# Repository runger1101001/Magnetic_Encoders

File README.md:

# Small encoder boards

Several designs for small magnetic encoder boards.
These boards all serve the same purpose, and many have the same shapes. They use different sensor ICs, which depending on the IC may result in different performance or different interface types.

They are intended to sense the absolute angular position of a rotating magnet. Generally this is used to sense the position of a motor shaft, as an input to motor control algorithms, or a joint/actuator position, for robotics applcations.

Where sensors use I2C, they use the Stemma-QT/Qwiic connectors (JST-SH) and pinouts.
Where sensors use SPI or SSI, they all use the same pinouts.

:warning: Not all of these have been produced or tested.

Please consult the individual subdirectories for more information. If a sub-directory does not contain a README, use at your own risk.

## Finished and tested designs

- [AS5048A](./Encoder_SPI/)
- [AS5048B](./Encoder/)
- [TLE5012B](./Encoder_SPI_TLE5012B/)
- [SC60228](./Encoder_SPI_SC60228/)

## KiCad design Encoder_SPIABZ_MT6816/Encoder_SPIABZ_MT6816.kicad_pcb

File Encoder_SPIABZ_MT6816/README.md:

# MT6816 magnetic angle sensor

Small (21x17mm) board for the MT6816 magnetic absolute angle sensor.

For use in motor control or robotics applications, the sensor measures the orientation (angle in the plane) of a nearby diametrically magnetized magnet.

That sounds more complicated than using it really is, so lets describe it another way:

- attach the magnet to the axis of something that rotates
- put the sensor near it
- read angles with your Arduino

| Back of board                                                               | Front of board                                                    |
| --------------------------------------------------------------------------- | ----------------------------------------------------------------- |
| with SH 1.0 connectors <br> | with sensor <br> |

## Features

- 3V to 5.5V operation
- 14 bit accuracy, 16384 positions per revolution
- SPI interface up to 15MHz
- PWM output pin with 1kHz PWM frequency and 12bit accuracy
- ABZ interface with 12 bit accuracy, 4096 steps in quadrature mode
- power indication LED (green, dim)

Datasheet of the sensor: https://www.novosns.com/enfiles/MT6816_Rev.2.1.pdf

## Getting one

You may be able to buy some here:

Or you could make one - it is open source, you will find gerber files and BOM in the repo, and design files for KiCad 6.

## Usage

The sensor has to be precisely positioned near the magnet. The magnet should be precisely on-axis and in-plane (no wobble!). The sensor should be mounted with an air-gap of about 0.5mm to the magnet.

Taking the time to mount the magnet and sensor board carefully will improve the accuracy and smoothness of your readings.

The sensor has SPI and ABZ interfaces, selectable by switch:

| SPI                                           | ABZ                                           |
| --------------------------------------------- | --------------------------------------------- |
|  |  |

The SPI and ABZ interfaces are output on a JST-SH 6-pin socket. Pre-made cables are available cheaply on AliExpress and other sources.

You may connect VCC to either 3.3V or 5V.

For SPI, connect the other lines (MOSI, MISO, CLK and CS) to the respective counterparts on your MCU board.
Note: The sensor board does not pull the CS line up.

The ABZ and SPI outputs cannot be used at the same time. Use the switch to select the output mode.

## Communications

SPI interface:

- SPI Mode 3
- MSB first
- max 15MHz SPI clock

See [datasheet](https://www.novosns.com/enfiles/MT6816_Rev.2.1.pdf) for details, or use an existing software driver.

:warning: Note: cable length, shielding (or lack thereof) and environmental noise may limit performance to significantly less than the 10MHz maximum.

## Software

The sensor can be used with any appropriate SPI driver.

The author uses it with Arduino-compatible MCU boards and the [SimpleFOC library](http://www.simplefoc.com).

A driver for the sensor for Arduino and SimpleFOC can be found here: [SimpleFOC drivers library](https://github.com/simplefoc/Arduino-FOC-drivers/tree/master/src/encoders/mt6816)

## Physical dimensions

v1.0: 21 x 17 x 4mm (1.6mm PCB)

## Cables

Pre-made JST SH 1.0 cables are available. When buying cables with two plugs, choose the type that is called "reverse connection" - where the pins on both ends of the cable have the same order.

Some links to compatible cables / breakout boards:

- https://www.tindie.com/products/26431/
- https://www.aliexpress.com/item/4000421829259.html
- https://www.aliexpress.com/item/4001235017139.html
- https://www.pololu.com/product/4770
- https://www.pololu.com/product/4772

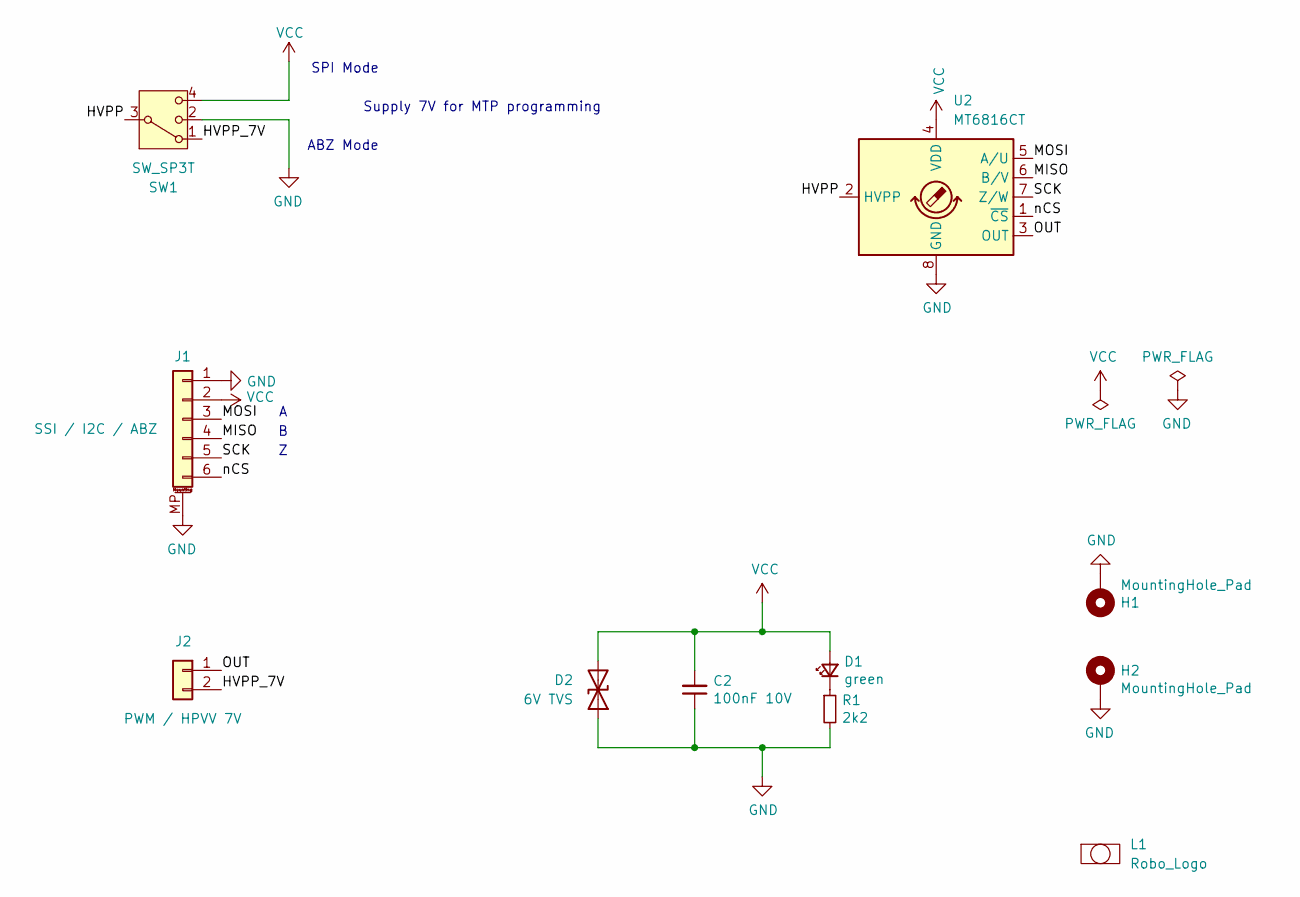
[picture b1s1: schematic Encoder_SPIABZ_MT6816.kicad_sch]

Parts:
C2: 100nF 10V; C_0603_1608Metric; Part GRM155R71A104KA01J
D1: green; LED_0603_1608Metric; Part 150040VS73240
D2: 6V TVS; D_0603_1608Metric; Part SP1005-01WTG
H1, H2: MountingHole_Pad; MountingHole_2.2mm_M2_ISO7380_Pad
J1: Conn_01x06_MountingPin; JST_SH_SM06B-SRSS-TB_1x06-1MP_P1.00mm_Horizontal; Part SCT-WR-S-06P
J2: Conn_01x02; PinHeader_1x02_P2.54mm_Vertical
L1: Robo_Logo; Robo_logo2
R1: 2k2; R_0603_1608Metric; Part Generic 2k2 Resistor
SW1: SW_SP3T; SLM-13-755-T50; Part SLM-13-755-T50; JLC C370968
U2: MT6816CT; SO-8_3.9x4.9mm_P1.27mm

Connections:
/HVPP: SW1.3, U2.2 (HVPP)
/HVPP_7V: J2.2, SW1.1
/MISO: J1.4, U2.6 (B/V)
/MOSI: J1.3, U2.5 (A/U)
/OUT: J2.1, U2.3 (OUT)
/SCK: J1.5, U2.7 (Z/W)
/nCS: J1.6, U2.1 (~CS)
GND: C2.1, D2.1 (A1), H1.1, H2.1, J1.1, J1.MP (MountPin), R1.2, SW1.2, SW1.MP, U2.8 (GND)
unnamed: D1.1 (K), R1.1
VCC: C2.2, D1.2 (A), D2.2 (A2), J1.2, SW1.4, U2.4 (VDD)

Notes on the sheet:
ABZ Mode
Supply 7V for MTP programming
SPI Mode

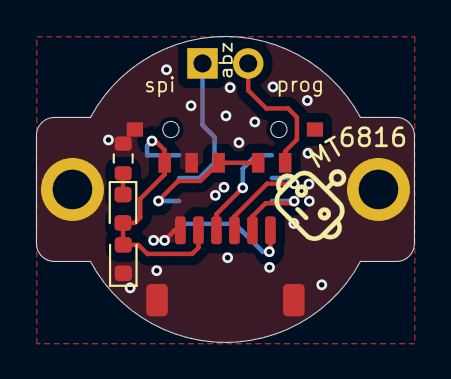
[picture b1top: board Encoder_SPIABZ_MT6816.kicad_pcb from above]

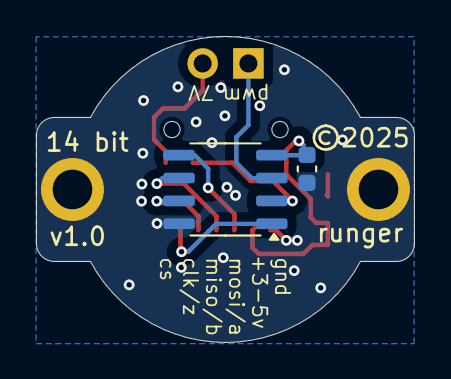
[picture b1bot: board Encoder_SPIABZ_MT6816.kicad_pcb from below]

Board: 2 copper layers, 21.0 x 17.0 mm, 11 parts (2 on the bottom side), 10 nets.

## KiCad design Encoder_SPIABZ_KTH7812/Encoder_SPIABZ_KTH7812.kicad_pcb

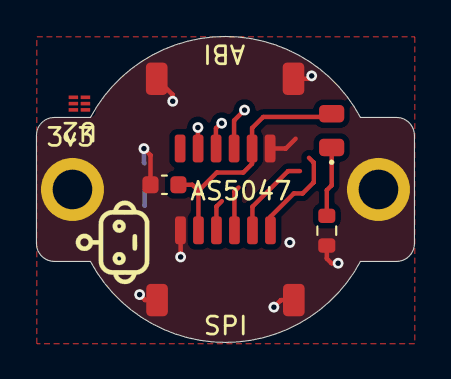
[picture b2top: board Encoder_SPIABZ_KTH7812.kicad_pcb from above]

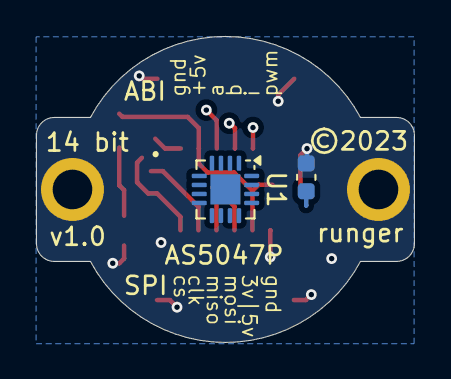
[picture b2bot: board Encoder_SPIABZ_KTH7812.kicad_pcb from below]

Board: 2 copper layers, 21.0 x 17.0 mm, 13 parts (2 on the bottom side), 13 nets.

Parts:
C1: 10uF 10V; C_0603_1608Metric
C2: 100nF 10V; C_0603_1608Metric
D1: green; LED_0805_2012Metric
H1, H2: MountingHole_Pad; MountingHole_2.2mm_M2_ISO7380_Pad
J1, J2: Conn_01x06_MountingPin; JST_SH_SM06B-SRSS-TB_1x06-1MP_P1.00mm_Horizontal
L1: Robo_Logo; Robo_logo2
R1: 2k2; R_0603_1608Metric
T1, T2: Tab
U1: KTH7812-X-X-QFN16-L; QFN-16-1EP_3x3mm_P0.5mm_EP1.675x1.675mm
U2: 74LVC1G97; DSF6

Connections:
/A: J2.3, U1.2 (A)
/B: J2.4, U1.6 (B)
/I: J2.5, U1.3 (Z)
/MGHL: J2.6, U2.4 (Y)
/MISO: J1.4, U1.7 (MISO)
/MOSI: J1.3, U1.4 (MOSI)
/SCK: J1.5, U1.12 (SCLK)
/nCS: J1.6, U1.5 (CS)
GND: C1.1, C2.1, H1.1, H2.1, J1.1, J1.MP (MountPin), J2.1, J2.MP (MountPin), R1.2, U1.8 (GND), U1.10 (TEST), U2.2 (GND), U2.3 (IN0)
unnamed: D1.1 (K), R1.1
unnamed: U1.16 (MGH), U2.1 (IN1)
unnamed: U1.11 (MGL), U2.6 (IN2)
VCC: C1.2, C2.2, D1.2 (A), J1.2, J2.2, U1.13 (VDD), U2.5 (VCC)

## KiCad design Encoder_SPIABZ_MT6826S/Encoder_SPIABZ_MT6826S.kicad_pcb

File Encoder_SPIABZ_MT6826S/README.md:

# MT6826S magnetic angle sensor

Small (21x17mm) board for the MT6826S magnetic absolute angle sensor.

For use in motor control or robotics applications, the sensor measures the orientation (angle in the plane) of a nearby diametrically magnetized magnet.

That sounds more complicated than using it really is, so lets describe it another way:
- attach the magnet to the axis of something that rotates
- put the sensor near it
- read angles with your Arduino

| Back of board | Front of board |
| --- | --- |
| with SH 1.0 connectors <br> | with sensor <br> |

## Features

- 3V to 5V operation
- 15 bit accuracy, 32768 positions per revolution 
- SPI interface up to 15Hz
- PWM output pin with 1kHz PWM frequency and 12bit accuracy
- ABZ interface with 14 bit accuracy, 16384 steps in quadrature mode
- power indication LED (green, dim)

Datasheet of the sensor: https://www.novosns.com/enfiles/MT6826S_Datasheet_Rev.1.1.pdf

## Getting one

You may be able to buy some here:

Or you could make one - it is open source, you will find gerber files and BOM in the repo, and design files for KiCad 6.

## Usage

The sensor has to be precisely positioned near the magnet. The magnet should be precisely on-axis and in-plane (no wobble!). The sensor should be mounted with an air-gap of about 0.5mm to the magnet.

Taking the time to mount the magnet and sensor board carefully will improve the accuracy and smoothness of your readings.

The sensor has SPI and ABZ interfaces:

|SPI|ABZ|
|---|---|
|||

The SPI interface is available on a JST-SH 6-pin socket. Pre-made cables are available cheaply on AliExpress and other sources.

You may connect VCC to either 3.3V or 5V, but must set the solder jumper accordingly. The default setting of the solder jumper is 3.3V. To use 5V power, carefully cut the trace connecting the two pads of the jumper. 

For SPI, connect the other lines (MOSI, MISO, CLK and CS) to the respective counterparts on your MCU board.

The ABZ outputs can be used in parallel to the SPI interface.

Note: The sensor board does not pull the CS line up.

## Communications

SPI interface:
- SPI Mode 3
- MSB first
- max 15MHz SPI clock

See [datasheet](https://www.novosns.com/enfiles/MT6826S_Datasheet_Rev.1.1.pdf) for details, or use an existing software driver.

:warning: Note: cable length, shielding (or lack thereof) and environmental noise may limit performance to significantly less than the 10MHz maximum.

## Software

The sensor can be used with any appropriate SPI driver.

The author uses it with Arduino-compatible MCU boards and the [SimpleFOC library](http://www.simplefoc.com).

A driver for the sensor for Arduino and SimpleFOC can be found here: [SimpleFOC drivers library](https://github.com/simplefoc/Arduino-FOC-drivers/tree/master/src/encoders/mt6826s)

## Physical dimensions

v1.0: 21 x 17 x 4mm (1.6mm PCB)

## Cables

Pre-made JST SH 1.0 cables are available. When buying cables with two plugs, choose the type that is called "reverse connection" - where the pins on both ends of the cable have the same order.

Some links to compatible cables / breakout boards:

 - https://www.tindie.com/products/26431/
 - https://www.aliexpress.com/item/4000421829259.html
 - https://www.aliexpress.com/item/4001235017139.html
 - https://www.pololu.com/product/4770
 - https://www.pololu.com/product/4772

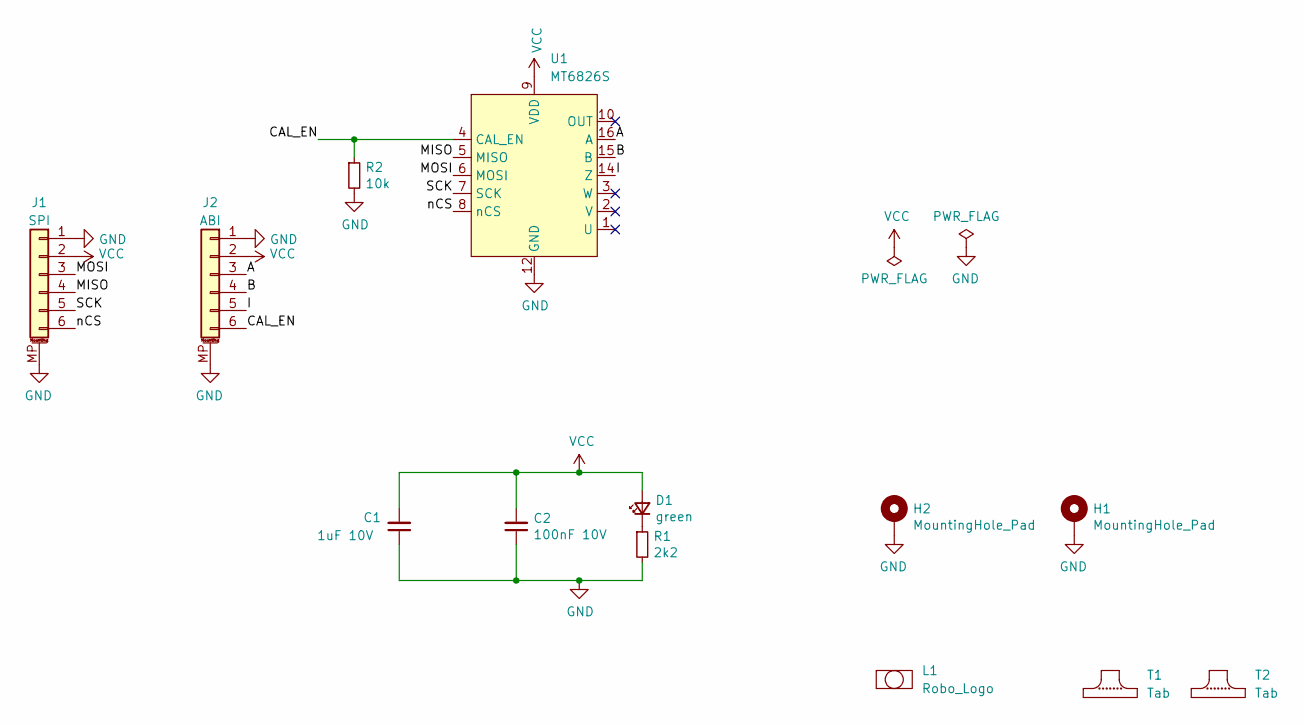
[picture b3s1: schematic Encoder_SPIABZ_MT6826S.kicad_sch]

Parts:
C1: 1uF 10V; C_0603_1608Metric; Part 1uF 10V
C2: 100nF 10V; C_0603_1608Metric; Part 100nF 10V
D1: green; LED_0805_2012Metric; Part Green LED
H1, H2: MountingHole_Pad; MountingHole_2.2mm_M2_ISO7380_Pad
J1, J2: Conn_01x06_MountingPin; JST_SH_SM06B-SRSS-TB_1x06-1MP_P1.00mm_Horizontal; Part SCT-WR-S-06P
L1: Robo_Logo; Robo_logo2
R1: 2k2; R_0603_1608Metric; Part Generic 2k2 Resistor
R2: 10k; R_0603_1608Metric; Part 10k
T1, T2: Tab
U1: MT6826S; TSSOP-16_4.4x5mm_P0.65mm; Part MT6835GT-STD

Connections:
/A: J2.3, U1.16 (A)
/B: J2.4, U1.15 (B)
/CAL_EN: J2.6, R2.1, U1.4 (CAL_EN)
/I: J2.5, U1.14 (Z)
/MISO: J1.4, U1.5 (MISO)
/MOSI: J1.3, U1.6 (MOSI)
/SCK: J1.5, U1.7 (SCK)
/nCS: J1.6, U1.8 (nCS)
GND: C1.1, C2.1, H1.1, H2.1, J1.1, J1.MP (MountPin), J2.1, J2.MP (MountPin), R1.2, R2.2, U1.12 (GND)
unnamed: D1.1 (K), R1.1
VCC: C1.2, C2.2, D1.2 (A), J1.2, J2.2, U1.9 (VDD)

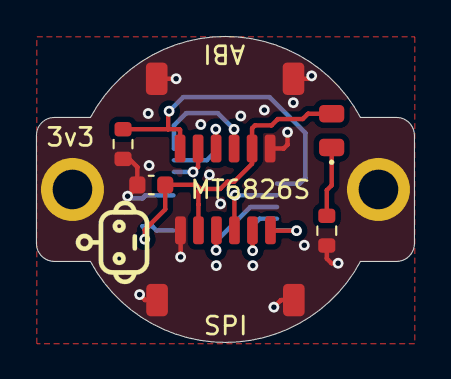
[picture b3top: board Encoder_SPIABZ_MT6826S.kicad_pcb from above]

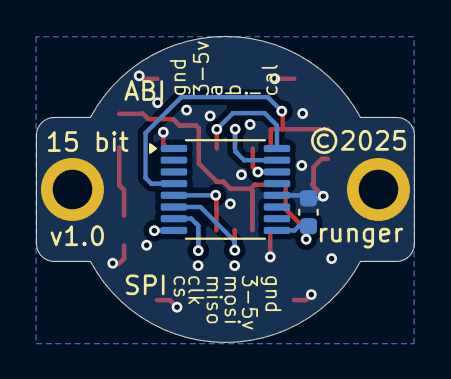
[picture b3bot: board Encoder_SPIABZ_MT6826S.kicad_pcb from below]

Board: 2 copper layers, 21.0 x 17.0 mm, 13 parts (2 on the bottom side), 11 nets.

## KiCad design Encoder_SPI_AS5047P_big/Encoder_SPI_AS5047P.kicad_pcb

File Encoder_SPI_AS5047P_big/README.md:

# AS5047P magnetic angle sensor

Small (21x17mm) board for the AS5047P magnetic absolute angle sensor.

For use in motor control or robotics applications, the sensor measures the orientation (angle in the plane) of a nearby diametrically magnetized magnet.

That sounds more complicated than using it really is, so lets describe it another way:
- attach the magnet to the axis of something that rotates
- put the sensor near it
- read angles with your Arduino

| Back of board | Front of board |
| --- | --- |
| with SH 1.0 connectors <br> | with sensor <br> |

## Features

- 3V to 5V operation
- 14 bit accuracy, 16384 positions per revolution 
- SPI interface up to 10MHz
- PWM output pin with 1kHz PWM frequency and 12bit accuracy
- ABZ interface with 12 bit accuracy, 4096 steps in quadrature mode
- power indication LED (green, dim)

Datasheet of the sensor: https://ams.com/documents/20143/36005/AS5047P_DS000324_3-00.pdf

## Getting one

You may be able to buy some here:

Or you could make one - it is open source, you will find gerber files and BOM in the repo, and design files for KiCad 6.

## Usage

The sensor has to be precisely positioned near the magnet. The magnet should be precisely on-axis and in-plane (no wobble!). The sensor should be mounted with an air-gap of about 0.5mm to the magnet.

Taking the time to mount the magnet and sensor board carefully will improve the accuracy and smoothness of your readings.

The sensor has SPI and ABZ interfaces:

|SPI|ABZ|
|---|---|
|||

The SPI interface is available on a JST-SH 6-pin socket. Pre-made cables are available cheaply on AliExpress and other sources.

You may connect VCC to either 3.3V or 5V, but must set the solder jumper accordingly. The default setting of the solder jumper is 3.3V. To use 5V power, carefully cut the trace connecting the two pads of the jumper. 

For SPI, connect the other lines (MOSI, MISO, CLK and CS) to the respective counterparts on your MCU board.

The ABZ outputs can be used in parallel to the SPI interface.

Note: The sensor board does not pull the CS line up.

## Communications

SPI interface:
- SPI Mode 1
- MSB first
- max 10MHz SPI clock

See [datasheet](https://ams.com/documents/20143/36005/AS5047P_DS000324_3-00.pdf) for details, or use an existing software driver.

:warning: Note: cable length, shielding (or lack thereof) and environmental noise may limit performance to significantly less than the 10MHz maximum.

## Software

The sensor can be used with any appropriate SPI driver.

The author uses it with Arduino-compatible MCU boards and the [SimpleFOC library](http://www.simplefoc.com).

A driver for the sensor for Arduino and SimpleFOC can be found here: [SimpleFOC drivers library](https://github.com/simplefoc/Arduino-FOC-drivers/tree/master/src/encoders/as5047)

## Physical dimensions

v1.0: 21 x 17 x 4mm (1.6mm PCB)

3D model: [STEP file](./Encoder_SPI_AS5047P.step)

## Cables

Pre-made JST SH 1.0 cables are available. When buying cables with two plugs, choose the type that is called "reverse connection" - where the pins on both ends of the cable have the same order.

Some links to compatible cables / breakout boards:

 - https://www.tindie.com/products/26431/
 - https://www.aliexpress.com/item/4000421829259.html
 - https://www.aliexpress.com/item/4001235017139.html
 - https://www.pololu.com/product/4770
 - https://www.pololu.com/product/4772

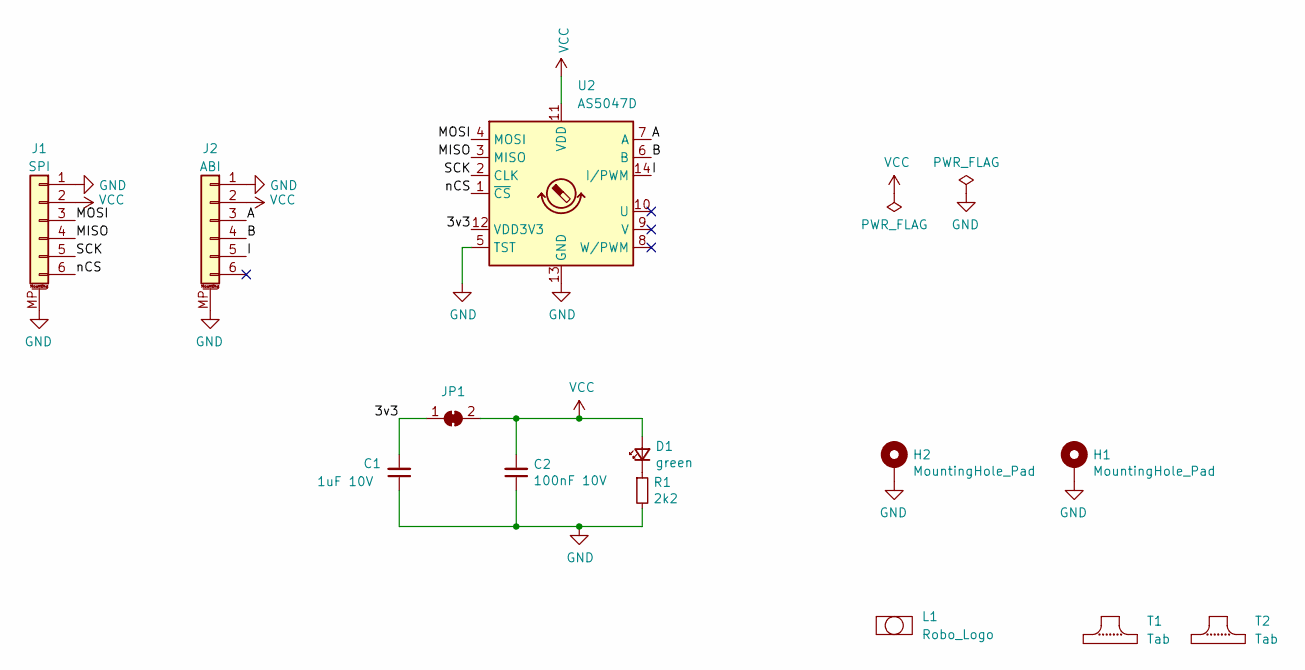
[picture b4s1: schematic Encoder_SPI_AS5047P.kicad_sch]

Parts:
C1: 1uF 10V; C_0603_1608Metric; Part 1uF 10V
C2: 100nF 10V; C_0603_1608Metric; Part 100nF 10V
D1: green; LED_0805_2012Metric; Part Green LED
H1, H2: MountingHole_Pad; MountingHole_2.2mm_M2_ISO7380_Pad
J1, J2: Conn_01x06_MountingPin; JST_SH_SM06B-SRSS-TB_1x06-1MP_P1.00mm_Horizontal; Part SCT-WR-S-06P
JP1: SolderJumper_2_Bridged; SolderJumper-2_P1.3mm_Bridged_RoundedPad1.0x1.5mm
L1: Robo_Logo; Robo_logo2
R1: 2k2; R_0603_1608Metric; Part Generic 2k2 Resistor
T1, T2: Tab
U2: AS5047D; TSSOP-14_4.4x5mm_P0.65mm; Part AS5047U-HTSM or

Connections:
/3v3: C1.2, JP1.1 (A), U2.12 (VDD3V3)
/A: J2.3, U2.7 (A)
/B: J2.4, U2.6 (B)
/I: J2.5, U2.14 (I/PWM)
/MISO: J1.4, U2.3 (MISO)
/MOSI: J1.3, U2.4 (MOSI)
/SCK: J1.5, U2.2 (CLK)
/nCS: J1.6, U2.1 (~CS)
GND: C1.1, C2.1, H1.1, H2.1, J1.1, J1.MP (MountPin), J2.1, J2.MP (MountPin), R1.2, U2.5 (TST), U2.13 (GND)
unnamed: D1.1 (K), R1.1
VCC: C2.2, D1.2 (A), J1.2, J2.2, JP1.2 (B), U2.11 (VDD)

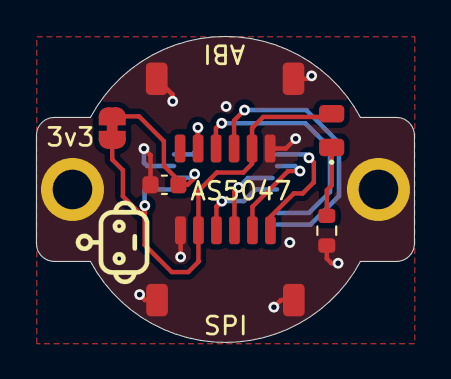
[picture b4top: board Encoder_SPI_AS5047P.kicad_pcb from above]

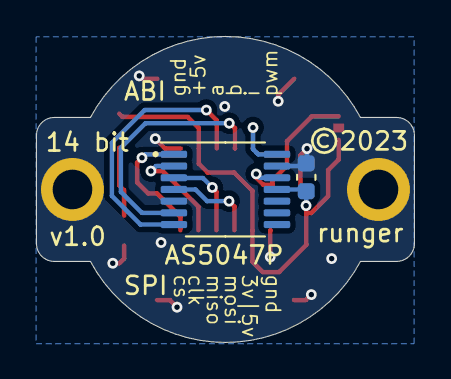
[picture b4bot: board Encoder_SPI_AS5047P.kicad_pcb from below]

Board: 2 copper layers, 21.0 x 17.0 mm, 13 parts (2 on the bottom side), 11 nets.

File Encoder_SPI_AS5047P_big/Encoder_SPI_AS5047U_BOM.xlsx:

Item | Ref Des | Qty | Manufacturer | Mfg Part # | Description / Value | Package | Type | Your Instructions / Notes
1 | C1 | 1 | Generic | 1uF 10V | 1uF 10V | C_0603_1608Metric | SMD | eg. YAGEO CC0603KRX7R6BB105; Unpolarized capacitor;
2 | C2 | 1 | Generic | 100nF 10V | 100nF 10V | C_0603_1608Metric | SMD | eg. YAGEO CC0603KRX7R6BB104; Unpolarized capacitor;
3 | D1 | 1 | Generic | Green LED | green | LED_0805_2012Metric | SMD | e.g. XINGLIGHT XL-2012UGC; Light emitting diode;
4 | J1,J2 | 2 | Scondar Electronic Limited | SCT-WR-S-06P | Conn_01x06_MountingPin | JST_SH_SM06B-SRSS-TB_1x06-1MP_P1.00mm_Horizontal | SMD | compatible to JST SH_SM06B-SRSS-TB_1x06-1MP_P1.00mm_Horizontal; Generic connect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
5 | R1 | 1 | Generic | Generic 4k7 Resistor | 4k7 | R_0603_1608Metric | SMD | ; Resistor;
6 | U2 | 1 | AMS | AS5047U-HTSM | AS5047P or AS5047U | TSSOP-14_4.4x5mm_P0.65mm | SMD | or AS5047P-ATSM, depends on price

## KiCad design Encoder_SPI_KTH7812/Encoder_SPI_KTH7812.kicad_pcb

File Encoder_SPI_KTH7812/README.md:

# KTH7812 magnetic angle sensor

Small (21x17mm) board for the KTH7812 magnetic absolute angle sensor with high resolution.

For use in motor control or robotics applications, the sensor measures the orientation (angle in the plane) of a nearby diametrically magnetized magnet.

That sounds more complicated than using it really is, so lets describe it another way:
- attach the magnet to the axis of something that rotates
- put the sensor near it
- read angles with your Arduino

| Back of board | Front of board |
| --- | --- |
| with SH 1.0 connector  | with sensor  |

## Features

- 3.3V to 5V operation
- 16 bit resolution, 65536 positions per revolution
- SPI interface up to 10MHz
- power indication LED (green, dim)

Datasheet of the sensor: [KTH7812_产品手册.pdf](https://en.conntek.com.cn/html/web/product/magneticAngleDetectionChip/hshrMagneticCodedAngleSensor/index.html
https://en.conntek.com.cn/api/resource/freeDownload?name=KTH7812%20产品手册.pdf)

## Getting one

You may be able to buy some here:

Or you could make one - it is open source, you will find gerber files and BOM in the repo, and design files for KiCad 9.

## Usage

The sensor has to be precisely positioned near the magnet. The magnet should be precisely on-axis and in-plane (no wobble!). The sensor should be mounted with an air-gap of about 0.5mm to the magnet.

Taking the time to mount the magnet and sensor board carefully will improve the accuracy and smoothness of your readings.

The sensor has an SPI interface:

The SPI interface is available on a JST-SH 6-pin socket. Pre-made cables are available cheaply on AliExpress and other sources.

You may connect VCC to either 3.3V or 5V. 

Connect the other lines (MOSI, MISO, CLK and CS) to the respective counterparts on your MCU board.

Note: The sensor board does not pull the CS line up.

## Communications

SPI interface:
- SPI Mode 3
- MSB first
- max 10MHz SPI clock

See [datasheet](https://en.conntek.com.cn/html/web/product/magneticAngleDetectionChip/hshrMagneticCodedAngleSensor/index.html
https://en.conntek.com.cn/api/resource/freeDownload?name=KTH7812%20产品手册.pdf) for details, or use an existing software driver.

:warning: Note: cable length, shielding (or lack thereof) and environmental noise may limit performance to significantly less than the 10MHz maximum.

## Software

The sensor can be used with any appropriate SPI driver.

The author uses it with Arduino-compatible MCU boards and the [SimpleFOC library](http://www.simplefoc.com).

A driver for the sensor for Arduino and SimpleFOC can be found here: [SimpleFOC drivers library](https://github.com/simplefoc/Arduino-FOC-drivers/tree/master/src/encoders/KTH7812)

## Physical dimensions

v1.0: 21 x 17 x 4mm (1.6mm PCB)

## Cables

Pre-made JST SH 1.0 cables are available. When buying cables with two plugs, choose the type that is called "reverse connection" - where the pins on both ends of the cable have the same order.

Some links to compatible cables / breakout boards:

 - https://www.tindie.com/products/26431/
 - https://www.aliexpress.com/item/4000421829259.html
 - https://www.aliexpress.com/item/4001235017139.html
 - https://www.pololu.com/product/4770
 - https://www.pololu.com/product/4772

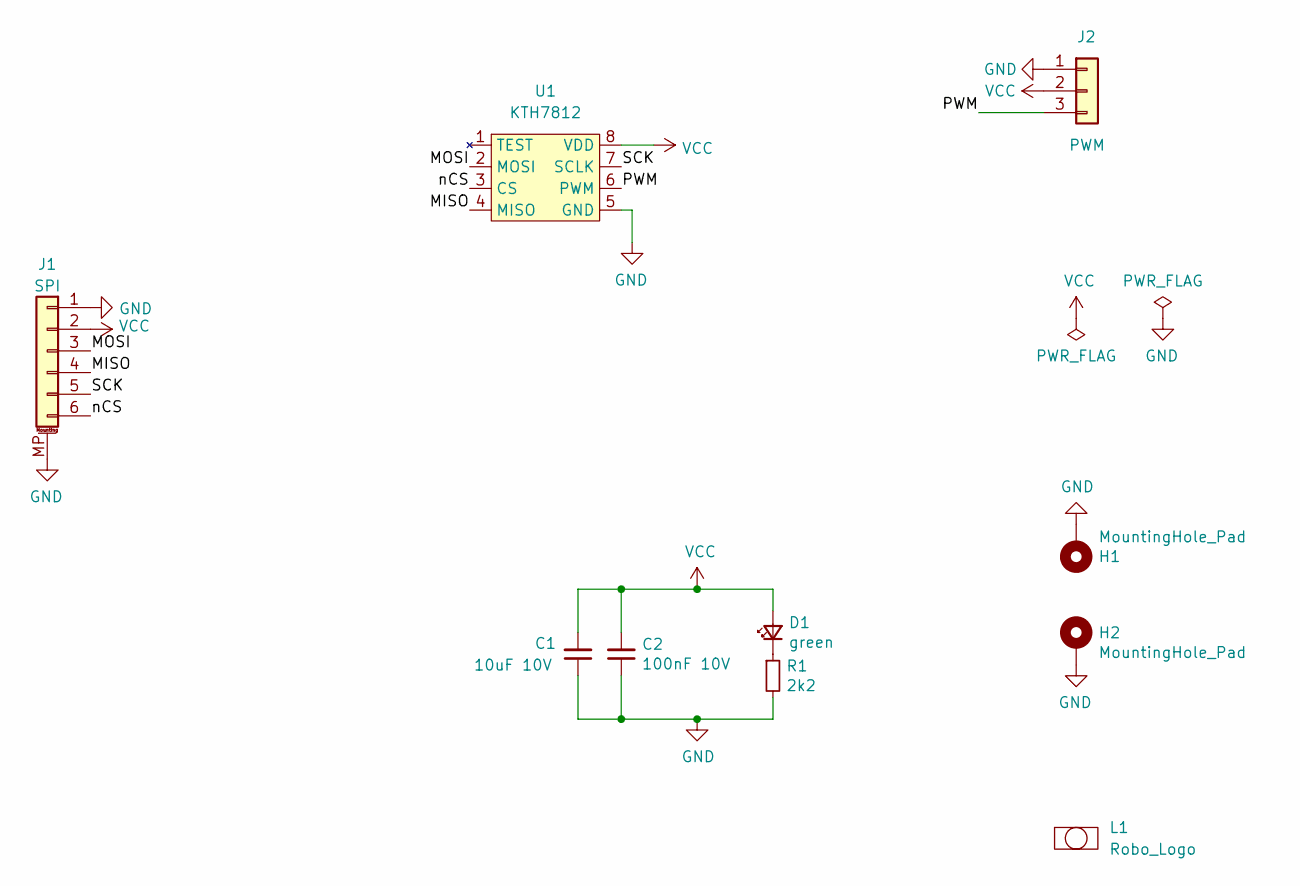
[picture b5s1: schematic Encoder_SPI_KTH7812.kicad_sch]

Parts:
C1: 10uF 10V; C_0805_2012Metric
C2: 100nF 10V; C_0603_1608Metric
D1: green; LED_0805_2012Metric
H1, H2: MountingHole_Pad; MountingHole_2.2mm_M2_ISO7380_Pad
J1: Conn_01x06_MountingPin; JST_SH_SM06B-SRSS-TB_1x06-1MP_P1.00mm_Horizontal; Part SCT-WR-S-06P
J2: Conn_01x03; PinHeader_1x03_P2.54mm_Vertical
L1: Robo_Logo; Robo_logo2
R1: 2k2; R_0805_2012Metric; Part Generic 2k2 Resistor
U1: KTH7812; SOP-8_3.76x4.96mm_P1.27mm

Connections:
/MISO: J1.4, U1.4 (MISO)
/MOSI: J1.3, U1.2 (MOSI)
/PWM: J2.3, U1.6 (PWM)
/SCK: J1.5, U1.7 (SCLK)
/nCS: J1.6, U1.3 (CS)
GND: C1.1, C2.1, H1.1, H2.1, J1.1, J1.MP (MountPin), J2.1, R1.2, U1.5 (GND)
unnamed: D1.1 (K), R1.1
VCC: C1.2, C2.2, D1.2 (A), J1.2, J2.2, U1.8 (VDD)

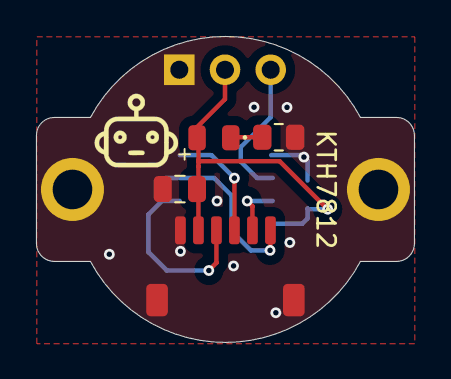
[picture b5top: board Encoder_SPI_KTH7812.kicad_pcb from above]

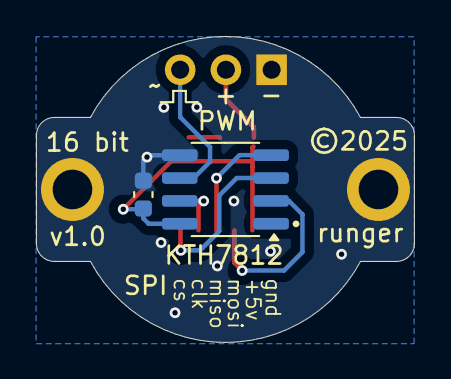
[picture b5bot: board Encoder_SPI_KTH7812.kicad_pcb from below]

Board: 2 copper layers, 21.0 x 17.0 mm, 10 parts (2 on the bottom side), 8 nets.

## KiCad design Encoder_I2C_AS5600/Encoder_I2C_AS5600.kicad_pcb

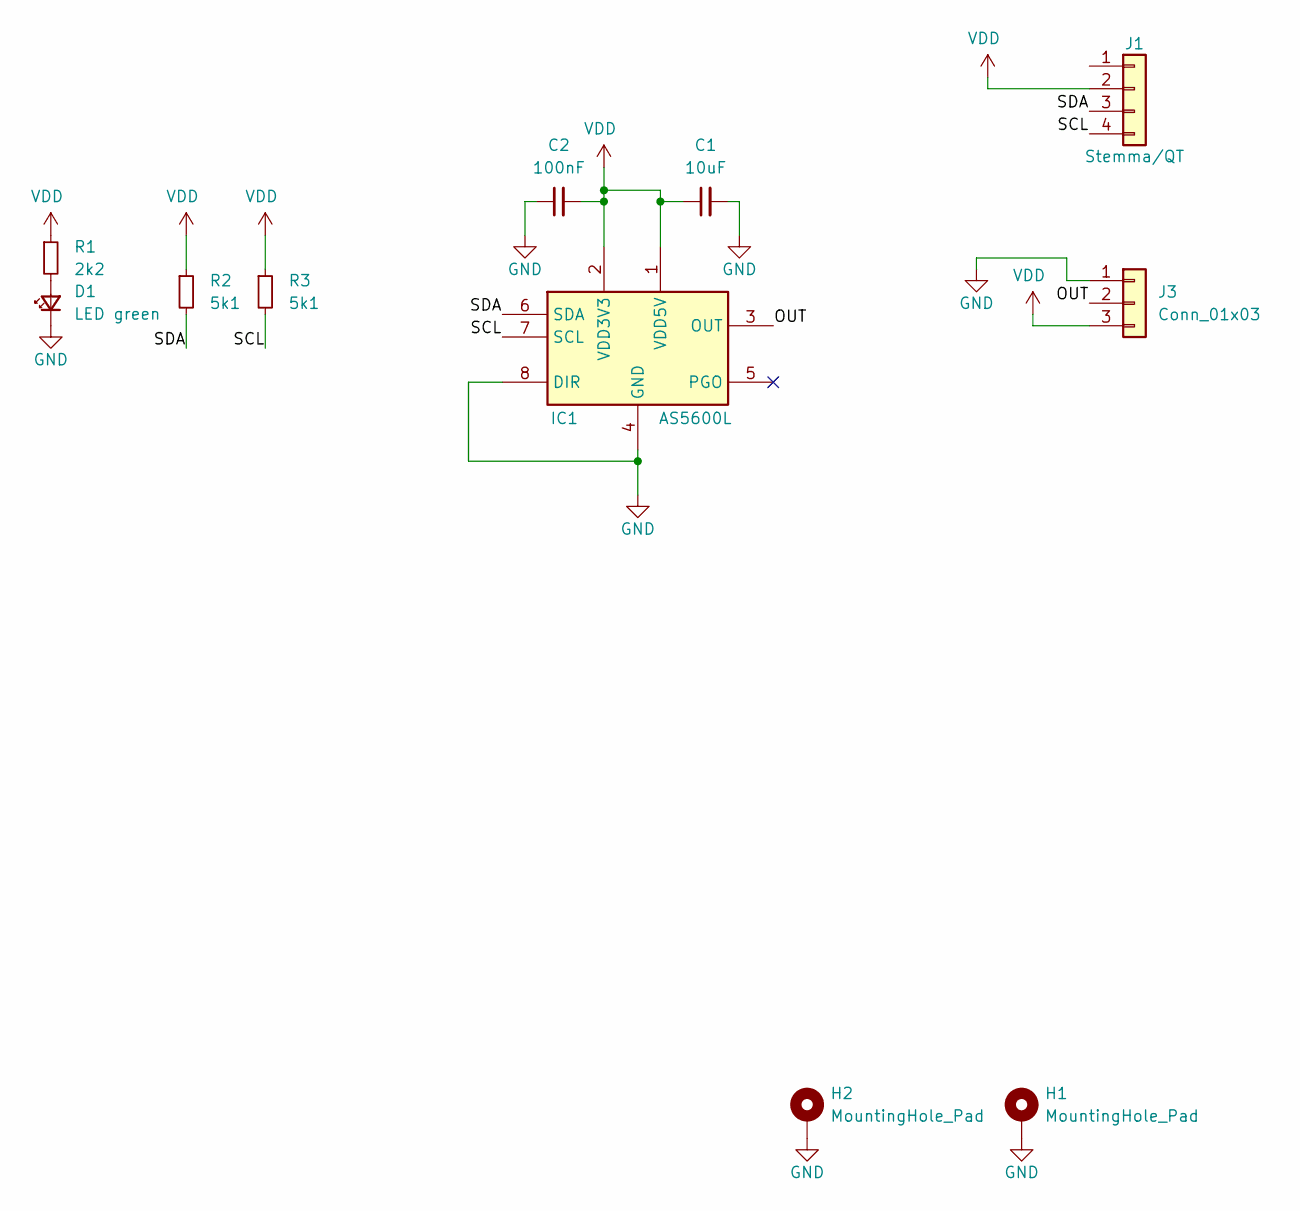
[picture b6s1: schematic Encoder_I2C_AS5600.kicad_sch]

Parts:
C1: 10uF; C_0603_1608Metric
C2: 100nF; C_0603_1608Metric
D1: LED green; LED_0603_1608Metric
H1, H2: MountingHole_Pad; MountingHole_2.2mm_M2_ISO7380_Pad
IC1: AS5600L; SOIC-8_3.9x4.9mm_P1.27mm; Part AS5600L-ASOM
J1: Conn_01x04; JST_SH_SM04B-SRSS-TB_1x04-1MP_P1.00mm_Horizontal; Part SH_SM04B-SRSS-TB_1x04-1MP
J3: Conn_01x03; PinHeader_1x03_P2.54mm_Vertical
R1: 2k2; R_0603_1608Metric
R2, R3: 5k1; R_0603_1608Metric

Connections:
/OUT: IC1.3 (OUT), J3.2
/SCL: IC1.7 (SCL), J1.4, R3.2
/SDA: IC1.6 (SDA), J1.3, R2.2
GND: C1.2, C2.1, D1.1 (K), H1.1, H2.1, IC1.4 (GND), IC1.8 (DIR), J3.1
unnamed: D1.2 (A), R1.2
VDD: C1.1, C2.2, IC1.1 (VDD5V), IC1.2 (VDD3V3), J1.2, J3.3, R1.1, R2.1, R3.1

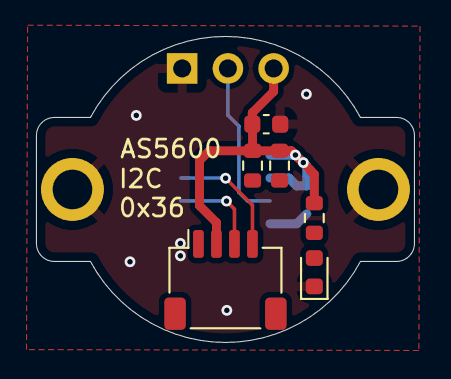
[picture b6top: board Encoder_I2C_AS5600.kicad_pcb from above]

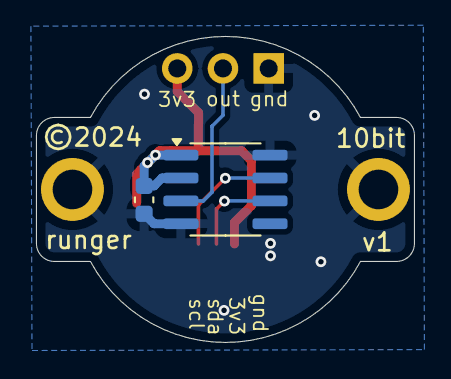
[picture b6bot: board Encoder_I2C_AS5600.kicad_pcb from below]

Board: 2 copper layers, 21.0 x 17.0 mm, 13 parts (2 on the bottom side), 6 nets.

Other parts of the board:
T1, T2: Tab

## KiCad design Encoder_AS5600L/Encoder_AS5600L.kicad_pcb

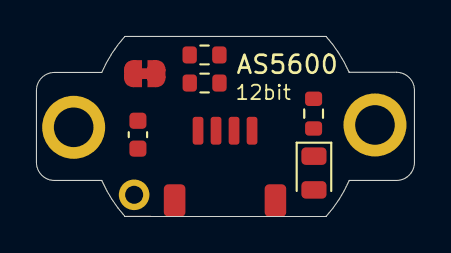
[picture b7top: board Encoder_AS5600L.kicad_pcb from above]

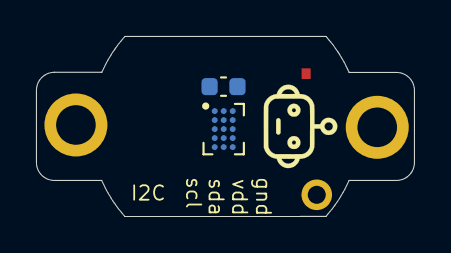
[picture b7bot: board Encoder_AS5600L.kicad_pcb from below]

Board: 2 copper layers, 21.0 x 10.0 mm, 12 parts (3 on the bottom side), 7 nets, no tracks yet.

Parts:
C1: 1uF 10V; C_0603_1608Metric
C2: 100nF 10V; C_0603_1608Metric
D1: green; LED_0805_2012Metric
H1, H2: MountingHole_Pad; MountingHole_2.2mm_M2_ISO7380_Pad
J1: JST_SH_SM04B; JST_SH_SM04B-SRSS-TB_1x04-1MP_P1.00mm_Horizontal
JP1: SolderJumper_2_Bridged; SolderJumper-2_P1.3mm_Bridged_RoundedPad1.0x1.5mm
L1: Robo_Logo; Robo_logo2
R1, R2, R3: 2k2; R_0603_1608Metric
U2: AS5600L; AS5600

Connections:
/3v3: C1.2, JP1.1 (A), U2.C3 (VDD3V3)
/SCL_A: J1.4, R1.2, U2.B1 (SCL)
/SDA_A: J1.3, R2.2, U2.D1 (SDA)
GND: C1.1, C2.1, H1.1, H2.1, J1.1, J1.MP (MountPin), R3.2, U2.A1 (DIR), U2.A2 (TEST), U2.C1 (TEST), U2.E2 (TEST), U2.E3 (GND)
unnamed: D1.1 (K), R3.1
VCC: C2.2, D1.2 (A), JP1.2 (B), U2.A3 (VDD5V), U2.E1 (PGO)
VDD: J1.2, R1.1, R2.1

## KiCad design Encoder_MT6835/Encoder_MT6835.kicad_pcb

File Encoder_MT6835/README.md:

# MT6835 magnetic angle sensor

Small (21x17mm) board for the MT6835 magnetic absolute angle sensor.

For use in motor control or robotics applications, the sensor measures the orientation (angle in the plane) of a nearby diametrically magnetized magnet.

That sounds more complicated than using it really is, so lets describe it another way:
- attach the magnet to the axis of something that rotates
- put the sensor near it
- read angles with your Arduino

| Back of board | Front of board |
| --- | --- |
| with SH 1.0 connectors <br> | with sensor <br> |

## Features

- 3V to 5V operation
- 21 bit accuracy, 2097152 positions per revolution (!)
- ABZ interface with 16 bit accuracy, 65536 steps in quadrature mode (!)
- SPI interface up to 15MHz
- PWM output pin with 994Hz PWM frequency and 12bit accuracy
- On-chip linearity calibration
- power indication LED (green, dim)

Datasheet of the sensor: https://www.magntek.com.cn/upload/MT6835_Rev.1.3.pdf

## Getting one

You may be able to buy some here:

Or you could make one - it is open source, you will find gerber files and BOM in the repo, and design files for KiCad 6.

## Usage

The sensor has to be precisely positioned near the magnet. The magnet should be precisely on-axis and in-plane (no wobble!). The sensor should be mounted with an air-gap of about 0.5mm to the magnet.

Taking the time to mount the magnet and sensor board carefully will improve the accuracy and smoothness of your readings.

The sensor has SPI and ABZ interfaces:

|SPI|ABZ|
|---|---|
|||

The SPI interface is available on a JST-SH 6-pin socket. Pre-made cables are available cheaply on AliExpress and other sources.

You may connect VCC to either 3.3V or 5V.

For SPI, connect the other lines (MOSI, MISO, CLK and CS) to the respective counterparts on your MCU board.

The ABZ outputs can be used in parallel to the SPI interface.

The CAL pin on the ABZ interface gives feedback on the built-in calibration procedure (see datasheet). It can be ignored if not needed.

Note: the sensor chip's ABZ interface is disabled by default. You have to enable it and set the resolution using the SPI interface.

Note: The sensor board does not pull the CS line up.

## Communications

SPI interface:
- SPI Mode 3
- MSB first
- max 15MHz SPI clock

See [datasheet](https://www.magntek.com.cn/upload/MT6835_Rev.1.3.pdf) for details, or use an existing software driver.

:warning: Note: cable length, shielding (or lack thereof) and environmental noise may limit performance to significantly less than the 15MHz maximum.

## Software

The sensor can be used with any appropriate SPI driver.

The author uses it with Arduino-compatible MCU boards and the [SimpleFOC library](http://www.simplefoc.com).

A driver for the sensor for Arduino and SimpleFOC can be found here: [SimpleFOC drivers library](https://github.com/simplefoc/Arduino-FOC-drivers/tree/master/src/encoders/mt6835)

## Physical dimensions

v1.0: 21 x 17 x 4mm (1.6mm PCB)

3D model: [STEP file](./Encoder_MT6835.step)

## Cables

Pre-made JST SH 1.0 cables are available. When buying cables with two plugs, choose the type that is called "reverse connection" - where the pins on both ends of the cable have the same order.

Some links to compatible cables / breakout boards:

 - https://www.tindie.com/products/26431/
 - https://www.aliexpress.com/item/4000421829259.html
 - https://www.aliexpress.com/item/4001235017139.html
 - https://www.pololu.com/product/4770
 - https://www.pololu.com/product/4772

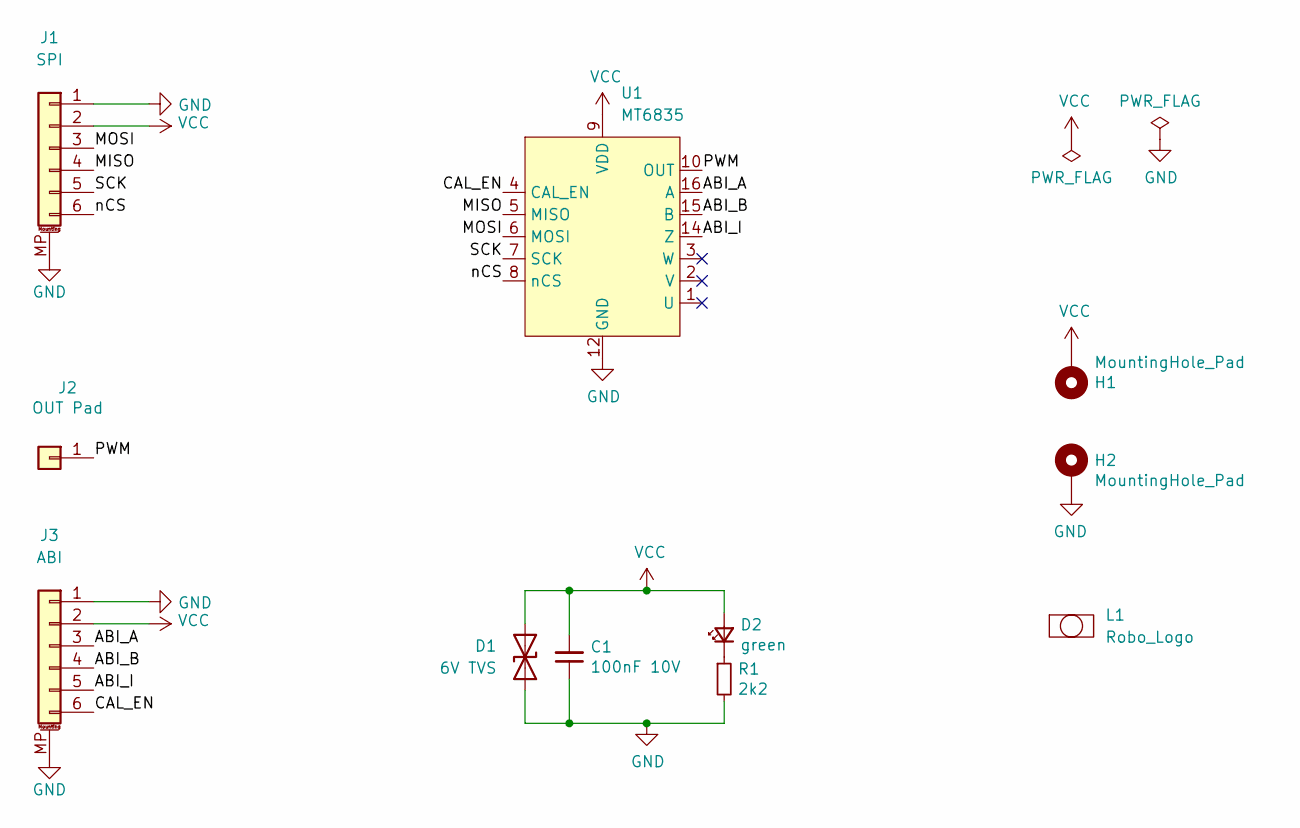
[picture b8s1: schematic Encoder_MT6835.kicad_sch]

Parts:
C1: 100nF 10V; C_0402_1005Metric; Part GRM155R71A104KA01J
D1: 6V TVS; D_0201_0603Metric; Part SP1005-01WTG
D2: green; LED_0402_1005Metric; Part 150040VS73240
H1, H2: MountingHole_Pad; MountingHole_2.2mm_M2_ISO7380_Pad
J1, J3: Conn_01x06_MountingPin; JST_SH_SM06B-SRSS-TB_1x06-1MP_P1.00mm_Horizontal; Part Connector_JST:JST_SH_SM06B-SRSS-TB_1x06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
J2: Pad_OUT; PinHeader_1x01_P2.54mm_Vertical
L1: Robo_Logo; Robo_logo2
R1: 2k2; R_0402_1005Metric; Part Generic 2k2 Resistor
U1: MT6835; TSSOP-16_4.4x5mm_P0.65mm; Part MT6835GT-STD

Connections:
/ABI_A: J3.3, U1.16 (A)
/ABI_B: J3.4, U1.15 (B)
/ABI_I: J3.5, U1.14 (Z)
/CAL_EN: J3.6, U1.4 (CAL_EN)
/MISO: J1.4, U1.5 (MISO)
/MOSI: J1.3, U1.6 (MOSI)
/PWM: J2.1, U1.10 (OUT)
/SCK: J1.5, U1.7 (SCK)
/nCS: J1.6, U1.8 (nCS)
GND: C1.1, D1.1 (A1), H2.1, J1.1, J1.MP (MountPin), J3.1, J3.MP (MountPin), R1.2, U1.12 (GND)
unnamed: D2.1 (K), R1.1
VCC: C1.2, D1.2 (A2), D2.2 (A), H1.1, J1.2, J3.2, U1.9 (VDD)

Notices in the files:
Encoder_I2C_AS5600/Encoder_I2C_AS5600.kicad_pcb:
©2024
Encoder_MT6835/Encoder_MT6835.kicad_pcb:
©2022
Encoder_SPIABZ_KTH7812/Encoder_SPIABZ_KTH7812.kicad_pcb:
©2023
Encoder_SPIABZ_MT6816/Encoder_SPIABZ_MT6816.kicad_pcb:
©2025
